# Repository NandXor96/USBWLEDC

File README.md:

# USBWLEDC
USB Sound Reactive WLED Controller

## Features

- USB-C for flashing and power (max. 3A)
- Small size (30mm x 35mm)
- Cheap components
- GSA4737 MEMS Microphone (similar to SPM1423)
- Solder Pads instead of Screw Terminal Blocks
- Files for panelized version (4x4)
- Files for 3D printed case
- Front side can be populated by JLCPCB

## Case

## Entering Flash Mode

To enter the Flash mode of the USBWLEDC, simply hold down the button as you connect the USB cable to a computer.

## WLED Config

| Name | Value |
|------|-------|
| LED Output 1: GPIO | 32 |
| LED Output 2: GPIO | 33 |
| Button 0: GPIO | 0 |
| Digitalmic: Type | Generic I2S PDM |
| Digitalmic: Pin I2S SD | GPIO 23 |
| Digitalmic: Pin I2S WS | GPIO 22 |

## BOM

|Designators   |Footprint                                       |Quantity|Value                  |LCSC Part #|
|--------------|------------------------------------------------|--------|-----------------------|-----------|
|C1*, C2, C4|Capacitor_SMD:C_0603_1608Metric                           |3    |100nF                  |C14663  |
|C3, C5, C7 |Capacitor_SMD:C_0805_2012Metric                           |3    |10uF                   |C15850  |
|C6         |Capacitor_SMD:C_0603_1608Metric                           |1    |1uF                    |C15849  |
|C8         |Capacitor_SMD:CP_Elec_5x5.4                               |1    |100uF                  |C131115 |
|J10        |Connector_USB:USB_C_Receptacle_G-Switch_GT-USB-7010ASV    |1    |USB-C Receptacle       |C2988369|
|MK1*       |Microphone:Microphone-6pin                                |1    |GSA4737 MEMS Microphone|C5142171|
|R1*        |Resistor_SMD:R_0603_1608Metric                            |1    |100k                   |C25803  |
|R2, R3     |Resistor_SMD:R_0603_1608Metric                            |2    |10k                    |C25804  |
|R4, R5     |Resistor_SMD:R_0603_1608Metric                            |2    |5.1k                   |C23186  |
|SW1        |Button_Switch_SMD:SW_Push_1P1T_XKB_TS-1187A               |1    |Push Button Flash      |C318884 |
|U1         |Package_SO:SOP-8_3.9x4.9mm_P1.27mm                        |1    |CH340N                 |C2977777|
|U2         |Package_TO_SOT_SMD:SOT-223-3_TabPin2                      |1    |AMS1117-3.3            |C6186   |
|U3**       |RF_Module:ESP32-WROOM-32                                  |1    |ESP32-WROOM-32         |C701341 |

\* You can build it without the microphone. Then you don't need R1, C1 and MK1.

\*\* The ESP32-WROOM Module can be purchased at a lower cost on AliExpress.

## Assembly

When ordering from JLCPCB, you have the option to get the front side of the board pre-populated - A service I strongly endorse. Subsequently, you'll only need to solder the ESP32-WROOM module onto the reverse side. With sufficient flux, this task can be accomplished with relative ease.

For those looking to populate the whole board, I suggest using a hot plate or a reflow oven for the front side.

    Be careful to keep Isopropyl Alcohol away from the hole of the microphone when cleaning the board!

## Disclaimer

The circuit board provided on this GitHub repository is offered "as is," without any warranties or guarantees of any kind. By accessing and utilizing this circuit board, you acknowledge and agree that you do so at your own risk.

The creator and contributor of this repository, shall not be held responsible or liable for any damages, losses, or injuries that may occur as a result of building and / or using this circuit board. This includes but is not limited to any direct, indirect, consequential, or incidental damages.

Electricity is dangerous. Only attempt this project if you know what you're doing.

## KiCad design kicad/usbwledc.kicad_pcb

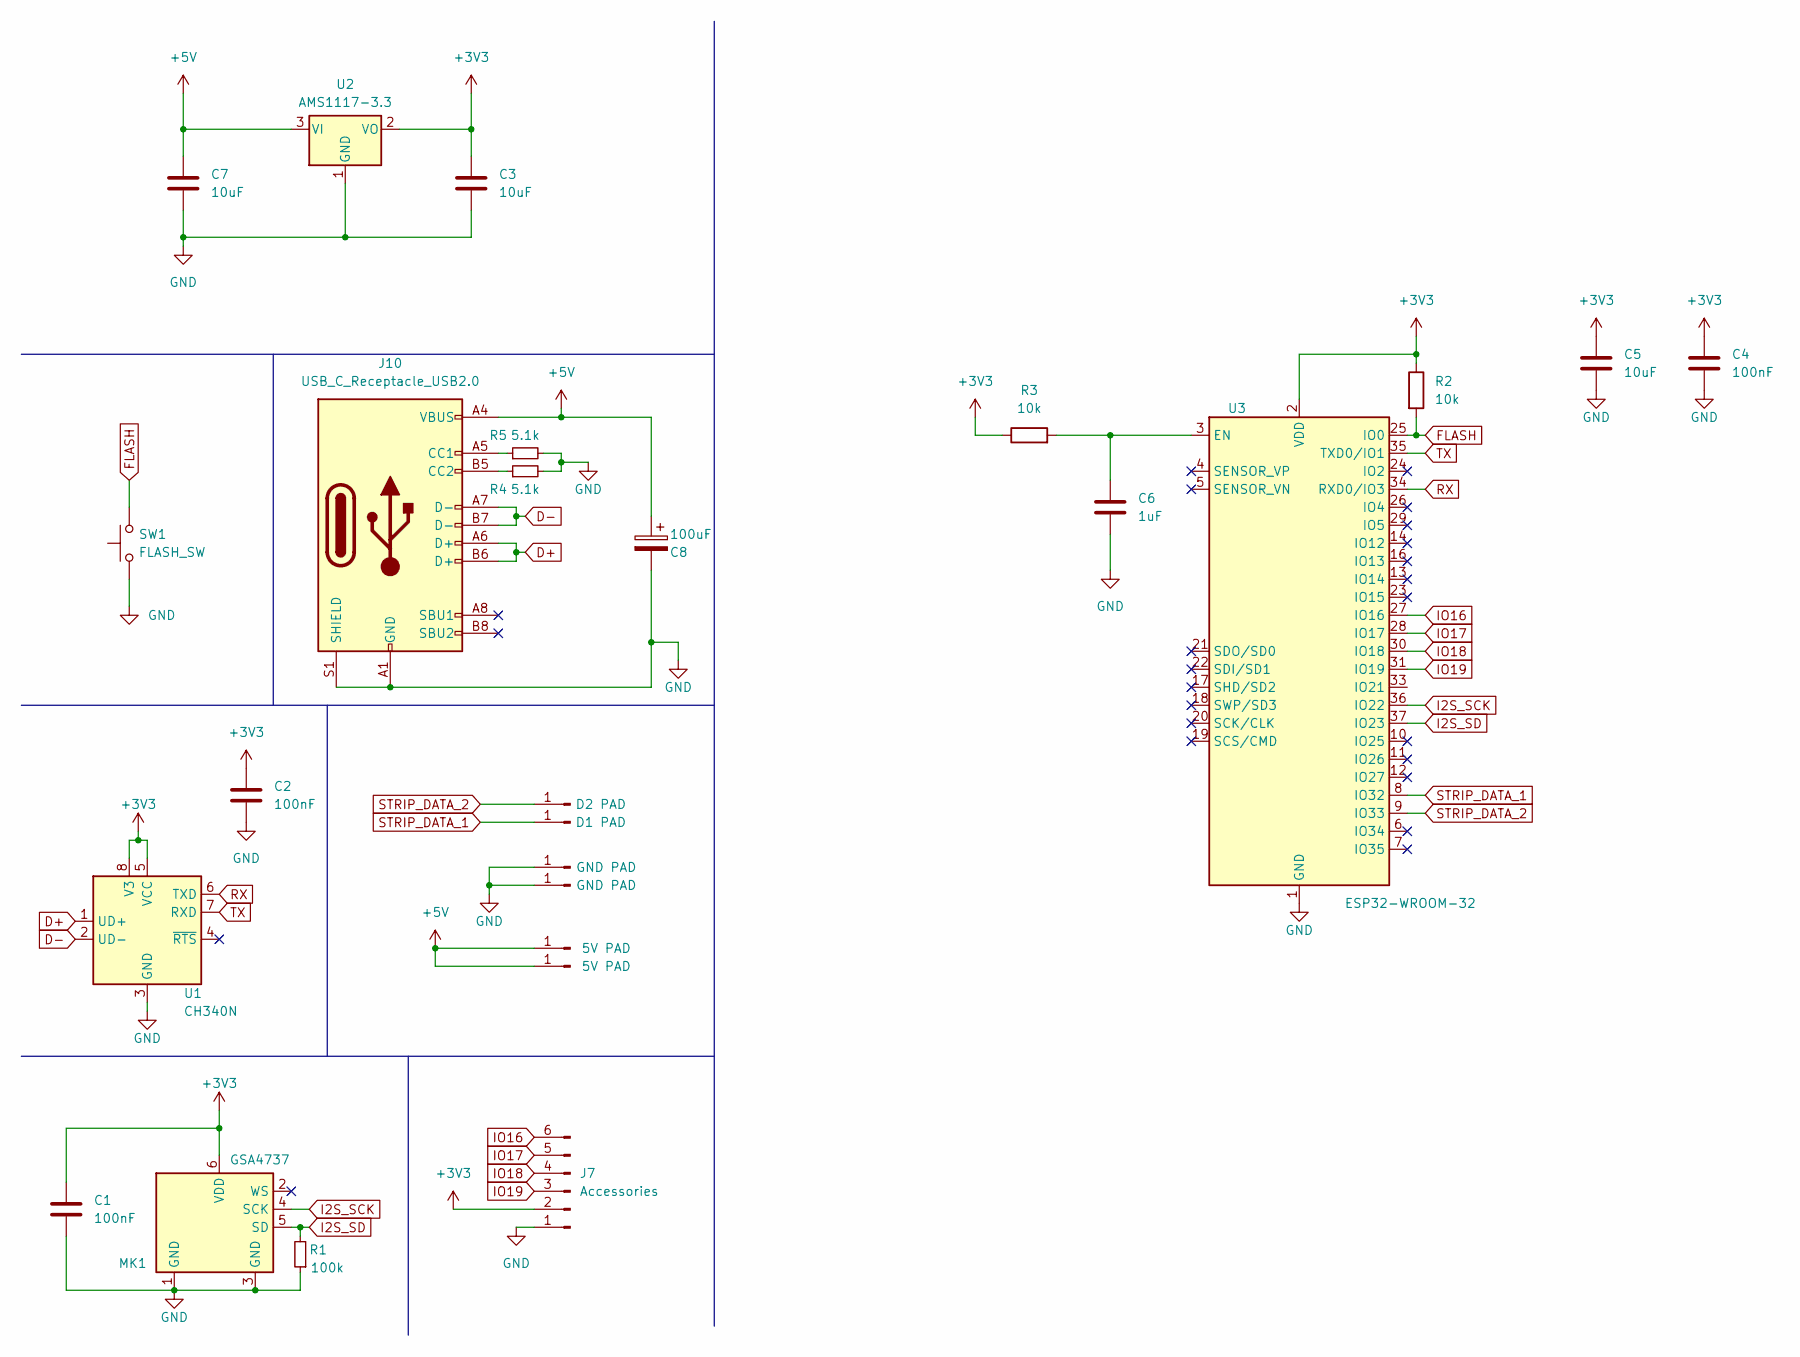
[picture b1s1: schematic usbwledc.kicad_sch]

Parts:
C1, C2, C4: 100nF; C_0603_1608Metric; MPN C14663
C3, C5, C7: 10uF; C_0805_2012Metric; MPN C15850
C6: 1uF; C_0603_1608Metric; MPN C15849
C8: 100uF; CP_Elec_5x5.4; MPN C131115
J1, J4: 5V PAD; SolderWirePad_1x01_SMD_3x6mm
J2: D1 PAD; SolderWirePad_1x01_SMD_3x6mm
J3, J6: GND PAD; SolderWirePad_1x01_SMD_3x6mm
J5: D2 PAD; SolderWirePad_1x01_SMD_3x6mm
J7: Accessories; PinHeader_1x06_P2.54mm_Vertical
J10: USB_C_Receptacle_USB2.0; USB_C_Receptacle_G-Switch_GT-USB-7010ASV; MPN C2988369
MK1: GSA4737; Microphone-6pin; MPN C5142171
R1: 100k; R_0603_1608Metric; MPN C25803
R2, R3: 10k; R_0603_1608Metric; MPN C25804
R4, R5: 5.1k; R_0603_1608Metric; MPN C23186
SW1: FLASH_SW; SW_Push_1P1T_XKB_TS-1187A; MPN C318884
U1: CH340N; SOP-8_3.9x4.9mm_P1.27mm; MPN C2977777
U2: AMS1117-3.3; SOT-223-3_TabPin2; MPN C6186
U3: ESP32-WROOM-32; MPN C701341; Mouser 356-ESP32WRM32E132PH

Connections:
+3V3: C1.1, C2.2, C3.1, C4.2, C5.1, J7.2, MK1.6 (VDD), R2.1, R3.1, U1.5 (VCC), U1.8 (V3), U2.2 (VO), U3.2 (VDD)
+5V: C7.1, C8.1, J1.1, J4.1, J10.A4 (VBUS), J10.A9 (VBUS), J10.B4 (VBUS), J10.B9 (VBUS), U2.3 (VI)
D+: J10.A6 (D+), J10.B6 (D+), U1.1 (UD+)
D-: J10.A7 (D-), J10.B7 (D-), U1.2 (UD-)
FLASH: R2.2, SW1.2, U3.25 (IO0)
GND: C1.2, C2.1, C3.2, C4.1, C5.2, C6.2, C7.2, C8.2, J3.1, J6.1, J7.1, J10.A1 (GND), J10.A12 (GND), J10.B1 (GND), J10.B12 (GND), J10.S1 (SHIELD), MK1.1 (GND), MK1.3 (GND), R1.1, R4.2, R5.2, SW1.1, U1.3 (GND), U2.1 (GND), U3.1 (GND), U3.15 (GND), U3.38 (GND), U3.39 (GND)
I2S_SCK: MK1.4 (SCK), U3.36 (IO22)
I2S_SD: MK1.5 (SD), R1.2, U3.37 (IO23)
IO16: J7.6, U3.27 (IO16)
IO17: J7.5, U3.28 (IO17)
IO18: J7.4, U3.30 (IO18)
IO19: J7.3, U3.31 (IO19)
unnamed: J10.A5 (CC1), R5.1
unnamed: J10.B5 (CC2), R4.1
unnamed: C6.1, R3.2, U3.3 (EN)
RELAY: U3.12 (IO27)
RX: U1.6 (TXD), U3.34 (RXD0/IO3)
STRIP_DATA_1: J2.1, U3.8 (IO32)
STRIP_DATA_2: J5.1, U3.9 (IO33)
TX: U1.7 (RXD), U3.35 (TXD0/IO1)

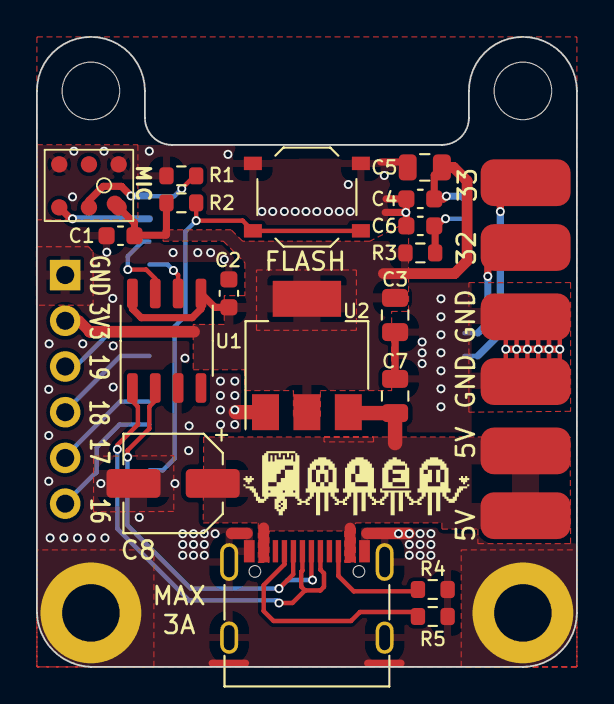
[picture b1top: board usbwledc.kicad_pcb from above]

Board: 2 copper layers, 30.0 x 35.0 mm, 30 parts (1 on the bottom side), 19 nets.

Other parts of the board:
H1, H2, H3, H4: MountingHole; MountingHole_3.2mm_M3_DIN965_Pad

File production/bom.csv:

Designator,Footprint,Quantity,Value,LCSC Part #
"C1, C2, C4",0805,3,100nF,C49678
"C3, C7",0805,2,22uF,C45783
C5,0805,1,10uF,C15850 
C6,0805,1,1uF,C28323
C8,CP_Radial_D8.0mm_P3.50mm,1,330uF,C3008476
"H1, H2, H3, H4",MountingHole_3.2mm_M3_DIN965_Pad_TopBottom,4,MountingHole,
"J1, J4",SolderWirePad_1x01_SMD_3x6mm,2,5V PAD,
J10,USB_C_Receptacle_G-Switch_GT-USB-7010ASV,1,USB_C_Receptacle_USB2.0,C2988369
J2,SolderWirePad_1x01_SMD_3x6mm,1,D1 PAD,
"J3, J6",SolderWirePad_1x01_SMD_3x6mm,2,GND PAD,
J5,SolderWirePad_1x01_SMD_3x6mm,1,D2 PAD,
J7,PinHeader_1x04_P2.54mm_Vertical,1,Conn_01x04_Pin,
MK1,InvenSense_ICS-43434-6_3.5x2.65mm,1,ICS-43434,
R1,0805,1,100k,C149504
"R2, R3",0805,2,10k,C17414
"R4, R5",0805,2,5.1k,C27834
SW1,SW_Tactile_SPST_NO_Straight_CK_PTS636Sx25SMTRLFS,1,FLASH_SW,C3726366
U1,SOP-8_3.9x4.9mm_P1.27mm,1,CH340N,C2977777
U2,SOT-223-3_TabPin2,1,AMS1117-3.3,C6186
U3,ESP32-WROOM-32,1,ESP32-WROOM-32,C701341

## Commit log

2023-08-13 Rename
2023-08-13 Small changes
2023-08-14 Rotated Resistor Value in Schematic
2024-04-11 v1.1
2024-04-11 Added real picture
2024-04-12 Added animated gif
